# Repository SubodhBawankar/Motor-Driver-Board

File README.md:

# Motor-Driver-Board
Motor Driver Board from Controlling Prestaltic Pump. Can control 4 such pumps.

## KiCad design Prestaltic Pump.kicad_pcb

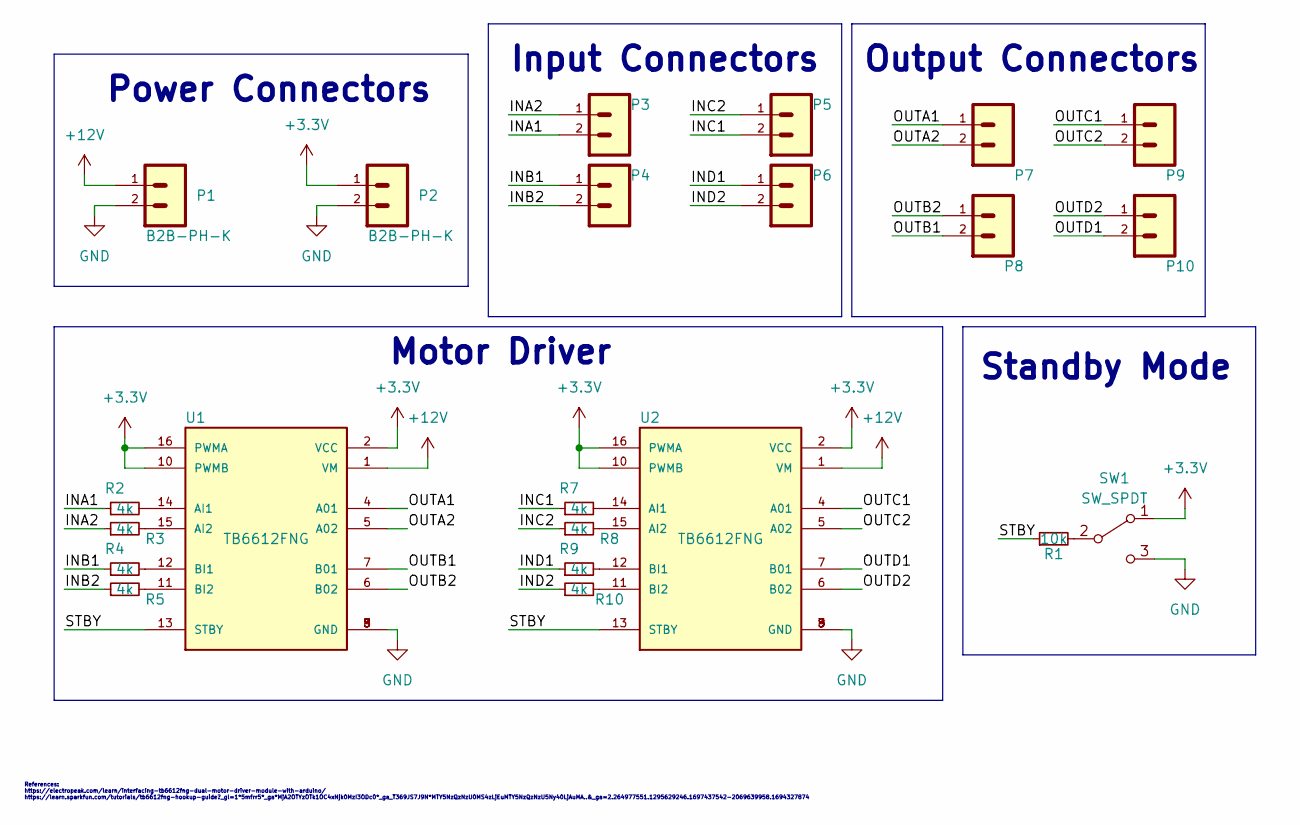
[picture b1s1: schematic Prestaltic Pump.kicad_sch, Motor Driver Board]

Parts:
P1, P2, P3, P4, P5, P6, P7, P8, P9, P10: B2B-PH-K
R1: 10k; R_Axial_DIN0204_L3.6mm_D1.6mm_P1.90mm_Vertical
R2, R3, R4, R5, R7, R8, R9, R10: 4k; R_Axial_DIN0204_L3.6mm_D1.6mm_P1.90mm_Vertical
SW1: SW_SPDT; SW_SPDT_PCM12
U1, U2: TB6612FNG; TB6612FNG_2; PARTREV 11-13-17

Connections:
+3.3V: P2.1, SW1.1 (A), U1.2 (VCC), U1.10 (PWMB), U1.16 (PWMA), U2.2 (VCC), U2.10 (PWMB), U2.16 (PWMA)
+12V: P1.1, U1.1 (VM), U2.1 (VM)
/INA1: P3.2, R2.1
/INA2: P3.1, R3.1
/INB1: P4.1, R4.1
/INB2: P4.2, R5.1
/INC1: P5.2, R7.1
/INC2: P5.1, R8.1
/IND1: P6.1, R9.1
/IND2: P6.2, R10.1
/OUTA1: P7.1, U1.4 (A01)
/OUTA2: P7.2, U1.5 (A02)
/OUTB1: P8.2, U1.7 (B01)
/OUTB2: P8.1, U1.6 (B02)
/OUTC1: P9.1, U2.4 (A01)
/OUTC2: P9.2, U2.5 (A02)
/OUTD1: P10.2, U2.7 (B01)
/OUTD2: P10.1, U2.6 (B02)
/STBY: R1.1, U1.13 (STBY), U2.13 (STBY)
GND: P1.2, P2.2, SW1.3 (C), U1.3 (GND), U1.8 (GND), U1.9 (GND), U2.3 (GND), U2.8 (GND), U2.9 (GND)
unnamed: R1.2, SW1.2 (B)
unnamed: R2.2, U1.14 (AI1)
unnamed: R3.2, U1.15 (AI2)
unnamed: R4.2, U1.12 (BI1)
unnamed: R5.2, U1.11 (BI2)
unnamed: R7.2, U2.14 (AI1)
unnamed: R8.2, U2.15 (AI2)
unnamed: R9.2, U2.12 (BI1)
unnamed: R10.2, U2.11 (BI2)

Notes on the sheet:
Output Connectors
Power Connectors
Motor Driver
Standby Mode
Input Connectors
References: https://electropeak.com/learn/interfacing-tb6612fng-dual-motor-driver-module-with-arduino/ https://learn.sparkfun.com/tutorials/tb6612fng-hookup-guide?_gl=1*5mfrr5*_ga*MjA2OTYzOTk1OC4xNjk0MzI3ODc0*_ga_T369JS7J9N*MTY5NzQzNzU0MS4zLjEuMTY5NzQzNzU5Ny40LjAuMA..&_ga=2.264977551.1295629246.169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

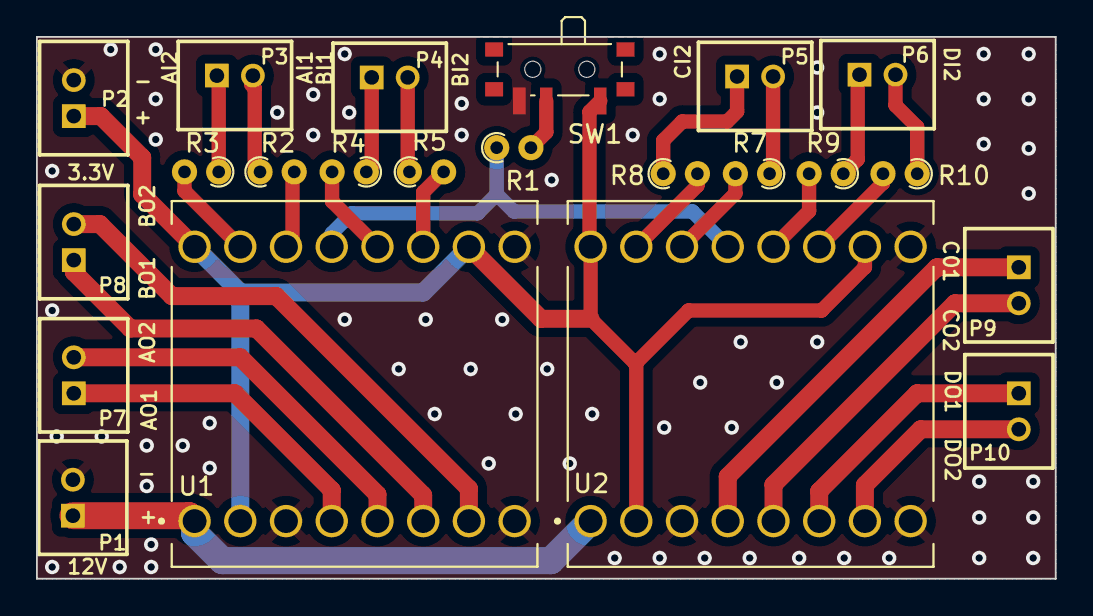
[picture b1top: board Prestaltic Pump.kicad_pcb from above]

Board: 2 copper layers, 56.6 x 30.1 mm, 22 parts (0 on the bottom side), 29 nets.

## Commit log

2023-10-19 Upload Project
